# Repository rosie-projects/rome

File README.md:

# Projeto ROME (Robótica Móvel nas Escolas)

## Sobre o Projeto
ROME é um projeto educacional dedicado a democratizar o acesso à educação em robótica para escolas públicas e comunidade. O projeto desenvolve ferramentas, materiais didáticos e minicursos de robótica, sendo uma iniciativa de hardware de código aberto que visa transformar alunos de consumidores passivos em desenvolvedores de soluções tecnológicas.

## Objetivos Principais
- Promover inclusão e transformação social através da robótica educacional
- Oferecer recursos flexíveis, de baixo custo e alta escalabilidade
- Estimular a cultura maker e aprendizagem prática
- Desenvolver habilidades como pensamento crítico, criatividade, comunicação e colaboração
- Integrar alunos do ensino médio ao ambiente universitário

## Estrutura do Projeto

```
rome/
├── Artigo/          # Documentação do projeto
├── PCB/         # Arquivos em PDF da esquemática da PCB
├── Plataforma Mecânica/           # Instruções para montagem da estrutura
│   ├── Prática/  # Pratica Docente e arquivos .ino
├── rome-conectado/   # Arquivos em KiCad na PCB

```

## Pré-requisitos

Para executar este projeto, você precisará ter instalado:

- Node.js (versão 14 ou superior)
- npm ou yarn
- Git
- Arduino IDE 1.8.19

## Componentes e Bibliotecas

### Hardware Necessário
- Placa Arduino
- Sensor ultrassônico HC-SR04
- Driver motor TB6612FNG

### Bibliotecas Arduino
1. **SparkFun TB6612FNG**
   - Biblioteca para controle dos motores
   - [Download SparkFun TB6612FNG](https://github.com/sparkfun/SparkFun_TB6612FNG_Arduino_Library)

2. **Ultrasonic**
   - Biblioteca para o sensor ultrassônico
   - [Download Ultrasonic](https://github.com/makerhero/Ultrasonic)

## Instalação

```bash
# Clone o repositório
git clone https://github.com/rosie-projects/rome.git

# Entre no diretório
cd rome

# Instale as dependências
npm install

# Inicie o servidor de desenvolvimento
npm run dev
```

## Como Usar

1. **Montagem do Hardware**
   - Monte a estrutura mecânica seguindo as instruções em `/Plataforma Mecânica`
   - Faça as conexões elétricas conforme o esquemático em `/PCB`
   - Conecte o Arduino, sensor ultrassônico e driver de motor

2. **Configuração do Software**
   - Abra o Arduino IDE 1.8.19
   - Instale as bibliotecas SparkFun TB6612FNG e Ultrasonic
   - Carregue o arquivo `/Prática/Pratica_final.ino`
   - Verifique se as portas definidas no código correspondem às suas conexões

3. **Execução**
   - Após carregar o código, o robô irá:
     - Mover-se para frente automaticamente
     - Detectar obstáculos usando o sensor ultrassônico
     - Desviar quando encontrar obstáculos a menos de 20cm

## Contribuição

1. Faça um Fork do projeto
2. Crie uma branch para sua feature (`git checkout -b feature/AmazingFeature`)
3. Commit suas mudanças (`git commit -m 'Add some AmazingFeature'`)
4. Push para a branch (`git push origin feature/AmazingFeature`)
5. Abra um Pull Request

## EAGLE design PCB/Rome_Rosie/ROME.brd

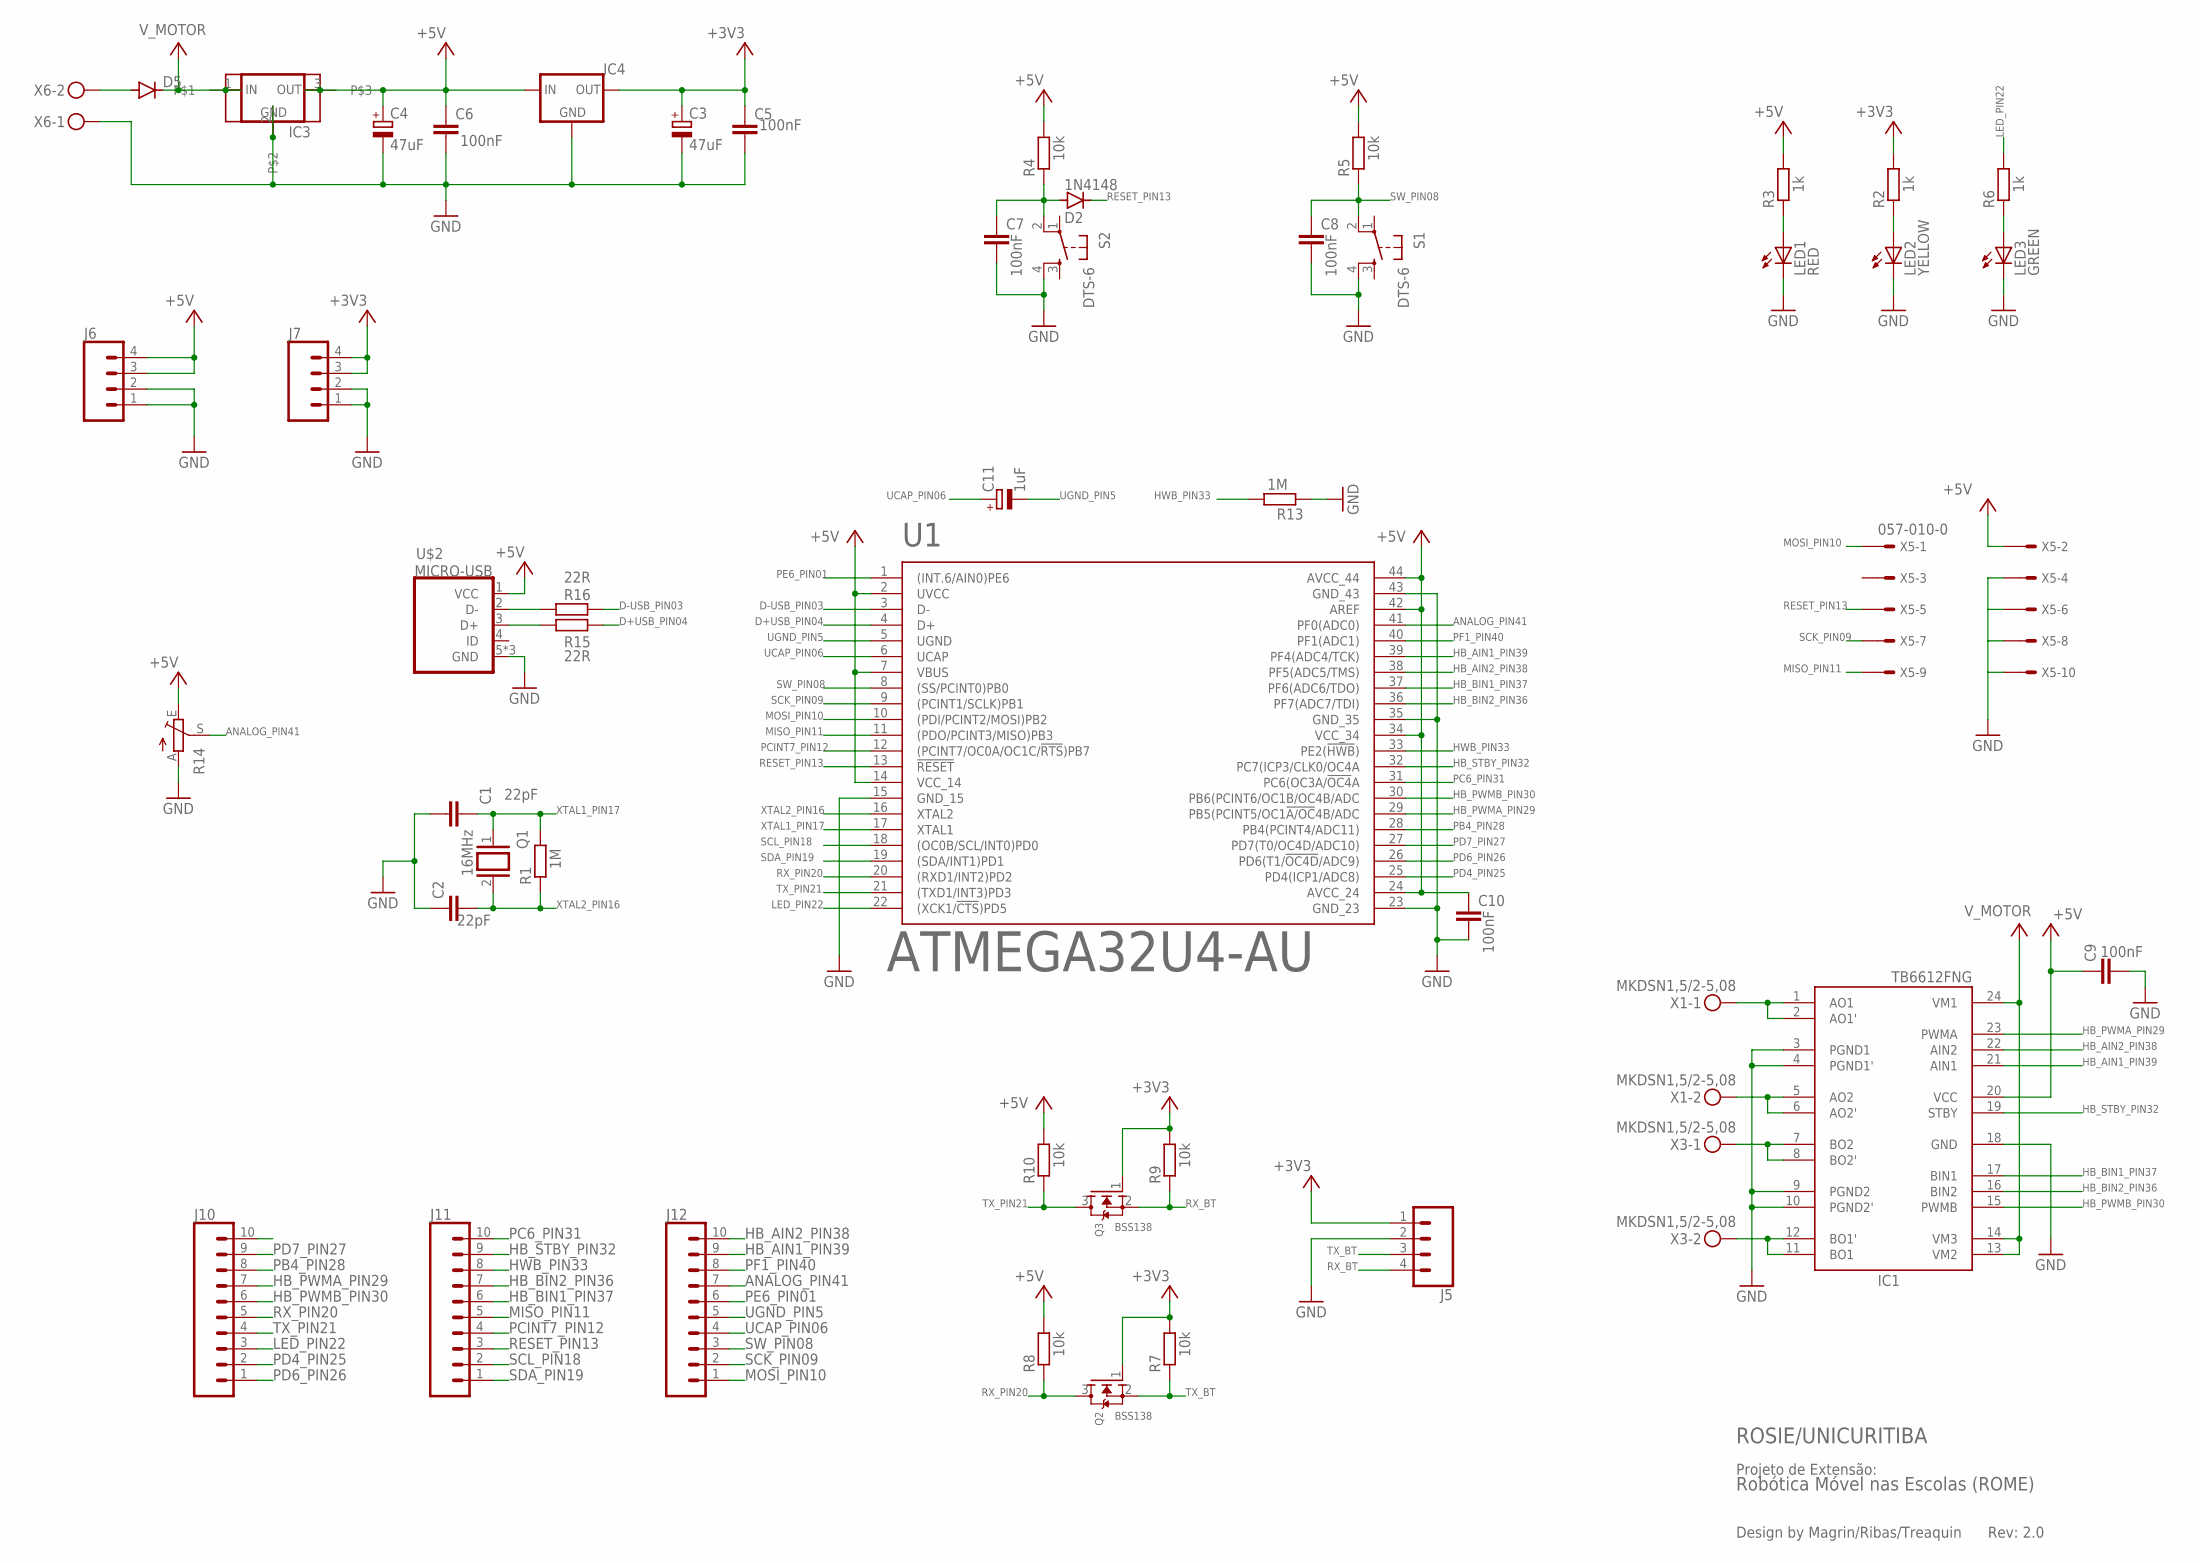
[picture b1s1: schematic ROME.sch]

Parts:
C1, C2: 22pF; C0805
C3, C4: 47uF; PANASONIC_C
C5, C6, C7, C8, C9, C10: 100nF; C0805
C11: 1uF; PANASONIC_C
D2: 1N4148; SOD80C
D5: DIODE-DO214AC; DO214AC
IC1: TB6612FNG; SSOP24
IC3: 78XXS
IC4: LM1117MP-3.3; SOT223
J5, J6, J7: CONN_04PTH; 1X04
J10, J11, J12: CONN_10"; 1X10
LED1: RED; CHIPLED_0805
LED2: YELLOW; CHIPLED_0805
LED3: GREEN; CHIPLED_0805
Q1: 16MHz; QS
Q2, Q3: BSS138; SOT23
R1, R13: 1M; R0805
R2, R3, R6: 1k; R0805
R4, R5, R7, R8, R9, R10: 10k; R0805
R14: TRIM_EU-CA6V; CA6V
R15, R16: 22R; R0805
S1, S2: DTS-6
U1: ATMEGA32U4-AU; 44-TQFP
U$2: MICRO-USB
U$4: DPACK
X1, X3, X6: MKDSN1,5/2-5,08
X5: 057-010-0

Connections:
+3V3: C3.+, C5.1, IC4.2 (OUT), IC4.4 (OUT), J5.1, J7.3, J7.4, Q2.1 (G), Q3.1 (G), R2.2, R7.2, R9.2
+5V: C4.+, C6.1, C9.1, C10.1, IC1.20 (VCC), IC3.OUT, IC4.3 (IN), J6.3, J6.4, R3.2, R4.2, R5.2, R8.2, R10.2, R14.E, U1.2 (UVCC), U1.7 (VBUS), U1.14 (VCC_14), U1.24 (AVCC_24), U1.34 (VCC_34), U1.42 (AREF), U1.44 (AVCC_44), U$2.1 (VCC), U$4.3, X5.2
ANALOG_PIN41: J12.7, R14.S, U1.41 (PF0(ADC0))
D+: R15.1, U$2.3 (D+)
D+USB_PIN04: R15.2, U1.4 (D+)
D-: R16.1, U$2.2 (D-)
D-USB_PIN03: R16.2, U1.3 (D-)
GND: C1.1, C2.1, C3.-, C4.-, C5.2, C6.2, C7.2, C8.2, C9.2, C10.2, IC1.3 (PGND1), IC1.4 (PGND1'), IC1.9 (PGND2), IC1.10 (PGND2'), IC1.18 (GND), IC3.GND, IC4.1 (GND), J5.2, J6.1, J6.2, J7.1, J7.2, LED1.C, LED2.C, LED3.C, R13.1, R14.A, S1.4, S2.4, U1.15 (GND_15), U1.23 (GND_23), U1.35 (GND_35), U1.43 (GND_43), U$2.5 (GND), U$2.GND1 (GND), U$2.GND2 (GND), U$4.2, X5.4, X5.6, X5.8, X5.10, X6.1
HB_AIN1_PIN39: IC1.21 (AIN1), J12.9, U1.39 (PF4(ADC4/TCK))
HB_AIN2_PIN38: IC1.22 (AIN2), J12.10, U1.38 (PF5(ADC5/TMS))
HB_AO1: IC1.1 (AO1), IC1.2 (AO1'), X1.1
HB_AO2: IC1.5 (AO2), IC1.6 (AO2'), X1.2
HB_BIN1_PIN37: IC1.17 (BIN1), J11.6, U1.37 (PF6(ADC6/TDO))
HB_BIN2_PIN36: IC1.16 (BIN2), J11.7, U1.36 (PF7(ADC7/TDI))
HB_BO1: IC1.11 (BO1), IC1.12 (BO1'), X3.2
HB_BO2: IC1.7 (BO2), IC1.8 (BO2'), X3.1
HB_PWMA_PIN29: IC1.23 (PWMA), J10.7, U1.29 (PB5(PCINT5/OC1!A/OC!4B/ADC)
HB_PWMB_PIN30: IC1.15 (PWMB), J10.6, U1.30 (PB6(PCINT6/OC1B/OC4B/ADC)
HB_STBY_PIN32: IC1.19 (STBY), J11.9, U1.32 (PC7(ICP3/CLK0/OC4A)
HWB_PIN33: J11.8, R13.2, U1.33 (PE2(!HWB!))
LED_PIN22: J10.3, R6.2, U1.22 ((XCK1/!CTS!)PD5)
MISO_PIN11: J11.5, U1.11 ((PDO/PCINT3/MISO)PB3), X5.9
MOSI_PIN10: J12.1, U1.10 ((PDI/PCINT2/MOSI)PB2), X5.1
unnamed: D5.A, X6.2
unnamed: LED1.A, R3.1
unnamed: LED2.A, R2.1
unnamed: C7.1, D2.A, R4.1, S2.2
unnamed: LED3.A, R6.1
PB4_PIN28: J10.8, U1.28 (PB4(PCINT4/ADC11))
PC6_PIN31: J11.10, U1.31 (PC6(OC3A/!OC4!A)
PCINT7_PIN12: J11.4, U1.12 ((PCINT7/OC0A/OC1C/!RTS!)PB7)
PD4_PIN25: J10.2, U1.25 (PD4(ICP1/ADC8))
PD6_PIN26: J10.1, U1.26 (PD6(T1/!OC4D!/ADC9))
PD7_PIN27: J10.9, U1.27 (PD7(T0/OC4D/ADC10))
PE6_PIN01: J12.6, U1.1 ((INT.6/AIN0)PE6)
PF1_PIN40: J12.8, U1.40 (PF1(ADC1))
RESET_PIN13: D2.C, J11.3, U1.13 (!RESET), X5.5
RX_BT: J5.4, Q3.2 (S), R9.1
RX_PIN20: J10.5, Q2.3 (D), R8.1, U1.20 ((RXD1/INT2)PD2)
SCK_PIN09: J12.2, U1.9 ((PCINT1/SCLK)PB1), X5.7
SCL_PIN18: J11.2, U1.18 ((OC0B/SCL/INT0)PD0)
SDA_PIN19: J11.1, U1.19 ((SDA/INT1)PD1)
SW_PIN08: C8.1, J12.3, R5.1, S1.2, U1.8 ((SS/PCINT0)PB0)
TX_BT: J5.3, Q2.2 (S), R7.1
TX_PIN21: J10.4, Q3.3 (D), R10.1, U1.21 ((TXD1/INT3)PD3)
UCAP_PIN06: C11.+, J12.4, U1.6 (UCAP)
UGND_PIN5: C11.-, J12.5, U1.5 (UGND)
V+: D5.C, IC1.13 (VM2), IC1.14 (VM3), IC1.24 (VM1), IC3.IN, U$4.1
XTAL1_PIN17: C1.2, Q1.1, R1.2, U1.17 (XTAL1)
XTAL2_PIN16: C2.2, Q1.2, R1.1, U1.16 (XTAL2)

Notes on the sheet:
Design by Magrin/Ribas/Treaquin
ROSIE/UNICURITIBA
Rev: 2.0
Projeto de Extensão:
Robótica Móvel nas Escolas (ROME)

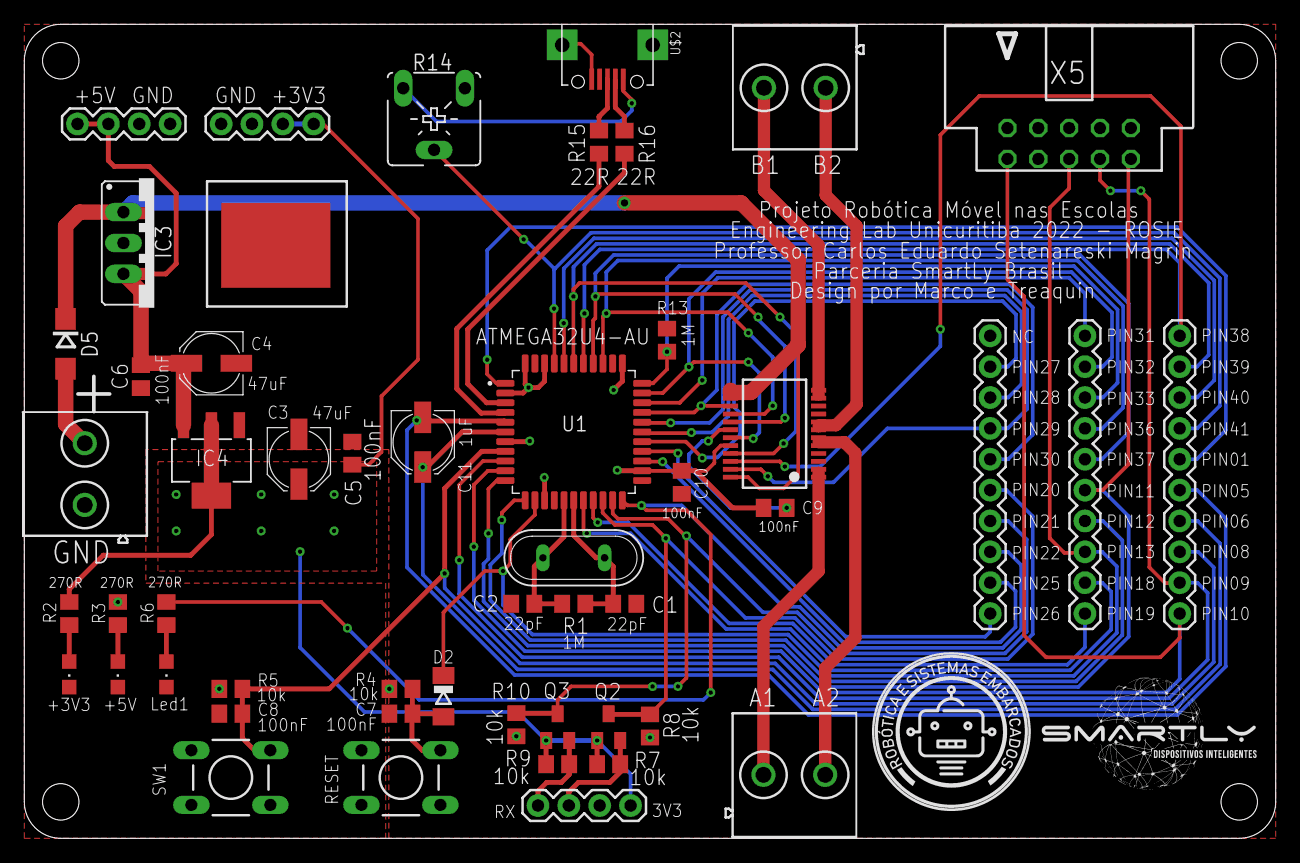
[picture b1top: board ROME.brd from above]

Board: 2 copper layers, 103.0 x 67.0 mm, 51 parts (0 on the bottom side), 50 nets.

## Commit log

2022-08-25 Projeto para corta em maquina CNC Router Laser
2022-08-25 Upload Projeto PCB e Artigo COTB
2022-08-25 Imagem da chapa MDF cortada
2022-08-25 Foto base montada
2024-06-06 Rename plataformaA4.jpeg to ROME - MDF CORTADA.jpeg1
2024-06-06 Rename Board1-1.pdf to Esquema da placa.pdf
2024-06-06 Rename BoardEx.pdf to Esquema da placa.pdf
2024-06-06 Rename Schematic.pdf to Esquemática da placa.pdf
2024-06-06 Prática
2025-05-30 Add KiCAD files of Rome Conectado
2025-06-02 Add ROSIE logo at the PCB
2025-06-11 Add gerber files
2025-06-12 Add missing drill files
2025-06-12 Update kicad project
2025-06-20 Update board after position adjustments
2025-08-19 update README & Artigo
2025-12-05 Reorganize papers directory
2025-12-05 Update project and WRE2026 paper

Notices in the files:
parts and their libraries:
SparkFun-Connectors: Licensing: Creative Commons ShareAlike 4.0 International - https://creativecommons.org/licenses/by-sa/4.0
